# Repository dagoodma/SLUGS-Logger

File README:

SLUGS-Logger

This is the code for a data logger currently being created at the UCSC Autonomous Systems Lab.

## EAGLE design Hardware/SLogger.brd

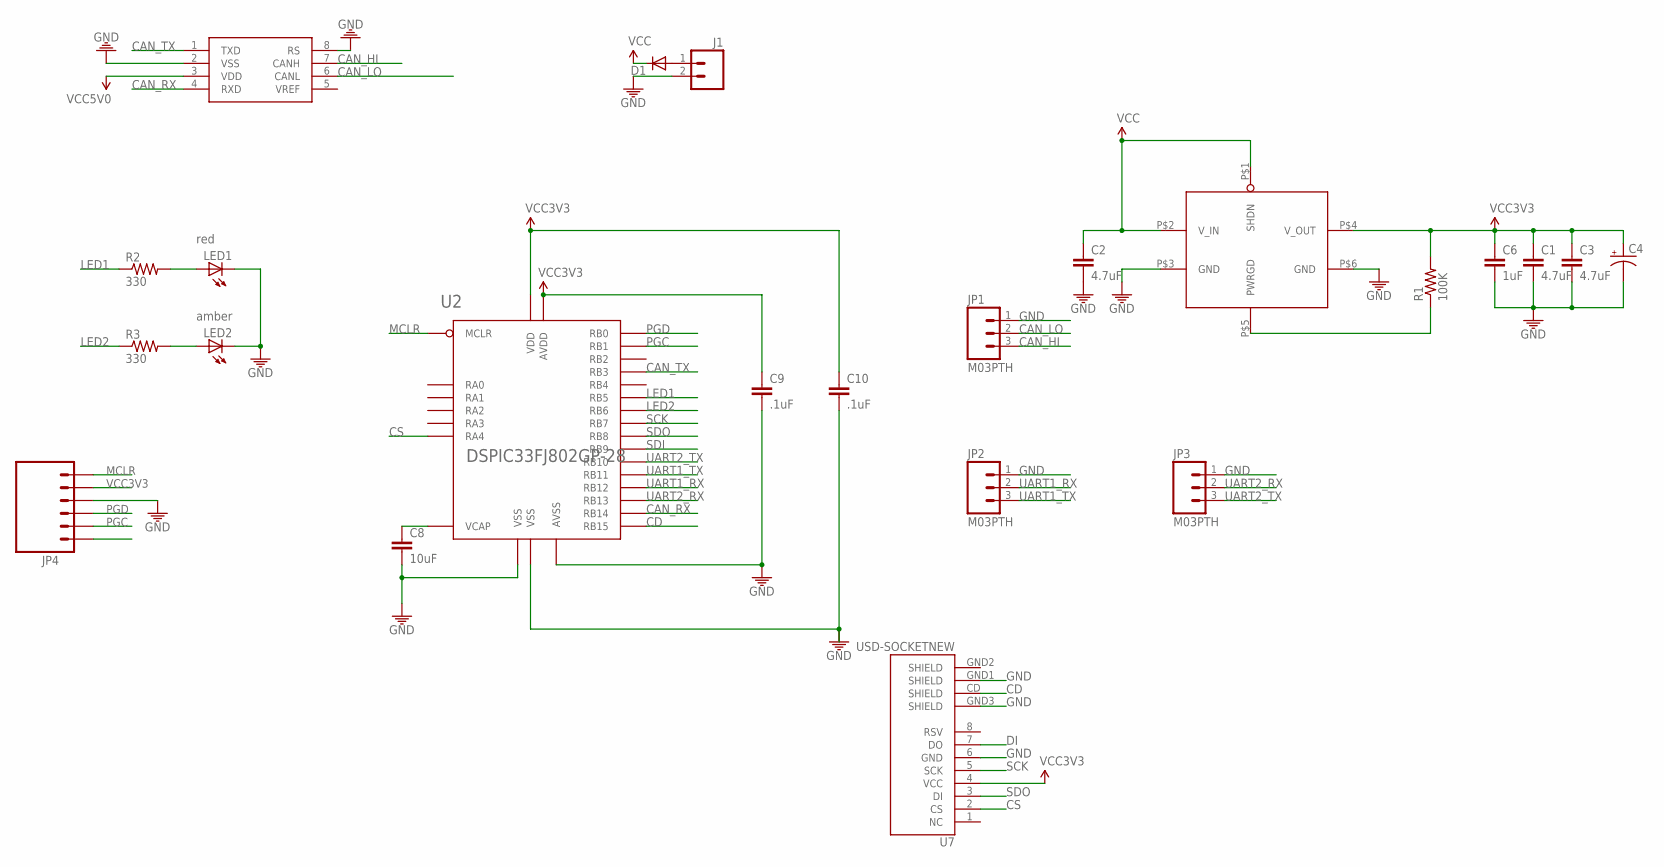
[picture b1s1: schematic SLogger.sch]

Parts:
C1, C2, C3: 4.7uF; 0805
C4: CAP_POLPTH1; CPOL-RADIAL-100UF-25V
C6: 1uF; 0805
C8: 10uF; 0805
C9, C10: .1uF; 0805
D1: DIODESOD; SOD-323F
J1: M02PTH; 1X02
JP1, JP2, JP3: M03PTH; 1X03
JP4: M06LOCK; 1X06_LOCK
LED1, LED2: LED0805; LED-0805
R1: 100K; 0805
R2, R3: 330; 0805
U2: DSPIC33FJ802GP-28; SOIC28-W
U4: MCP2551; SO08
U7: USD-SOCKETNEW; MICRO-SD-SOCKET-PP
U$2: MCP1826; SOT223-5

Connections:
CAN_HI: JP1.3, U4.7 (CANH)
CAN_LO: JP1.2, U4.6 (CANL)
CAN_RX: U2.P$25 (RB14), U4.4 (RXD)
CAN_TX: U2.P$7 (RB3), U4.1 (TXD)
CD: U2.P$26 (RB15), U7.CD (SHIELD)
CS: U2.P$12 (RA4), U7.2 (CS)
DI: U7.7 (DO)
GND: C1.2, C2.2, C3.2, C4.2 (-), C6.2, C8.2, C9.2, C10.2, J1.2 (1), JP1.1, JP2.1, JP3.1, JP4.4, LED1.2 (C), LED2.2 (C), U2.P$8 (VSS), U2.P$19 (VSS), U2.P$27 (AVSS), U4.2 (VSS), U4.8 (RS), U7.6 (GND), U7.GND1 (SHIELD), U7.GND3 (SHIELD)
GND@3: U$2.P$3 (GND)
GND@6: U$2.P$6 (GND)
LED1: R2.1, U2.P$14 (RB5)
LED2: R3.1, U2.P$15 (RB6)
MCLR: JP4.6, U2.P$1 (MCLR)
unnamed: LED1.1 (A), R2.2
unnamed: D1.2 (A), J1.1 (2)
unnamed: LED2.1 (A), R3.2
unnamed: R1.1, U$2.P$5 (PWRGD)
unnamed: C8.1, U2.P$20 (VCAP)
PGC: JP4.2, U2.P$5 (RB1)
PGD: JP4.3, U2.P$4 (RB0)
SCK: U2.P$16 (RB7), U7.5 (SCK)
SDI: U2.P$18 (RB9)
SDO: U2.P$17 (RB8), U7.3 (DI)
UART1_RX: JP2.2, U2.P$23 (RB12)
UART1_TX: JP2.3, U2.P$22 (RB11)
UART2_RX: JP3.2, U2.P$24 (RB13)
UART2_TX: JP3.3, U2.P$21 (RB10)
VCC: C2.1, D1.1 (C), U$2.P$1 (SHDN), U$2.P$2 (V_IN)
VCC3V3: C1.1, C3.1, C4.1 (+), C6.1, C9.1, C10.1, JP4.5, R1.2, U2.P$13 (VDD), U2.P$28 (AVDD), U7.4 (VCC), U$2.P$4 (V_OUT)
VCC5V0: U4.3 (VDD)

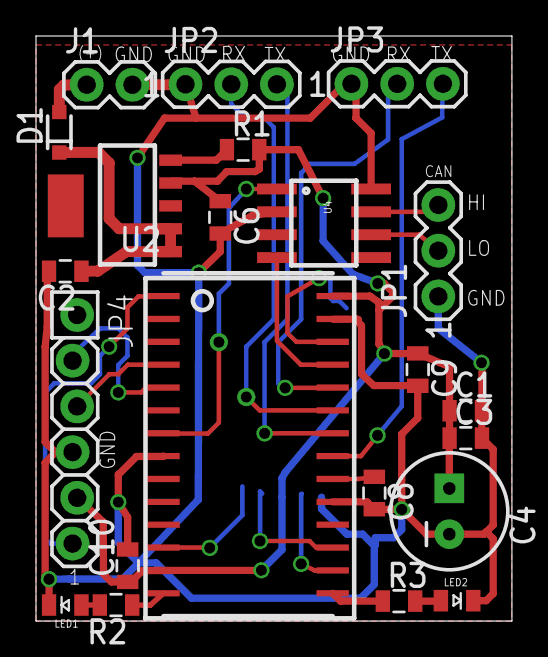
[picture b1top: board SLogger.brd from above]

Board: 2 copper layers, 26.4 x 32.5 mm, 23 parts (1 on the bottom side), 25 nets.

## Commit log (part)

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2013-02-19 Getting used to UART. This does simply receive using DMA.
2013-02-19 Put UART init and interrupt into Uart2.c and Uart2.h
2013-02-19 Put DMA stuff with Uart2 library. DMA is now in ping-pong mode.
2013-02-19 Finished ping-pong buffer with user-defined interrupt func. Uart2Init() now takes a user-defined function pointer which is called when a pin-pong buffer is full. main.c has an example.
2013-02-21 Copied many files from other folders into NewUARTDriver to support Service_SPI.
2013-02-22 Plugged old SPI and Filesystem stuff into new UART using OFBProxy to give Service_SPI() something to use.
2013-02-23 Added NewSDWrite to use unmodified FSIO functions to write to SD.
2013-02-27 Successfully writes multiple sectors into a single cluster. Hacks the FSIO lib.
2013-02-28 Added allocate_multiple_clusters and used it. Doesn't quite work correctly yet with skipping over used clusters.
2013-03-01 Now works with other files in the card and with multiple clusters.
2013-03-02 Added a single-shot sector-write function which does not currently work.
2013-03-05 NewSDWriteSector now works correctly. This easily allows writing a single sectors at a time to a file.
2013-03-05 Added new SDWrite functions to more versatile. They don't currently work. Updated the todo list.
2013-03-05 NewSDWriteSector and NewSDInit now work correctly using the function NewFileUpdate which mimics FSfclose.
2013-03-06 Added TODO.TXT
2013-03-06 More reworking of file system. Redownloaded Microchip lib and removed all old library code.
2013-03-06 Implemented Bryant's circular buffer to work with the UART. It kinda works. Only writes up to 33kb.
2013-03-06 Still getting 33k error, now has debug code. Added debug folder with interesting UART output. Seems there is a problem transitioning between clusters.
2013-03-06 Updated code an debug output, updated debug log to better reflect what is happening.
2013-03-07 33k bug is because of incorrect cluster switching.
2013-03-12 Fixed 33k bug - now correctly switches to a new cluster when needed.
2013-03-12 Data sent while SD is disconnected now is correctly written when the card is reconnected. The fix causes ~30% of sectors to be dropped when writing large files.
2013-03-13 Now only inits the SD card when it is reconnected, not every time we send.
2013-03-14 Added notes file with ideas about states of the card and a thought on allocation efficiency.
2013-03-15 Tested multiple times - each test had indentical errors. Now 38400 baud, removed some debug code.
2013-03-15 Included main.c file for the code used to produce a reliable serial output from a dsPIC33. Added test data and observations.
2013-03-15 Generates own data for putting on the circular buffer. Added more debug notes - a clear pattern was found. Not a problem with serial, DMA, or speed. See third debug note.
2013-03-16 Now the readme isn't totally blank.
2013-03-20 Continued testing to fix circular buffer bug - it is more complicated than expected. Created a python script to confirm a repeating text file.
2013-03-20 Edited readme.
2013-03-20 Changed README file extention to markdown.
2013-04-01 Fixed circular buffer bug, added tests to verify.
2013-04-03 Added more thorough test to CircularBuffer.c and removed a redundant if-else.
2013-04-03 Changed serial sender to send a large amount of text.
2013-04-08 Added checksums on the input and output of the circ buff. There is still a problem with reading from the circ buff.
2013-04-12 Cleaned up CB_Remove() and removed some debug checks.
2013-04-12 More cleanup.
2013-04-12 More cleanup, set things up to do a 3 hour full-speed test.
2013-04-12 Added book.h
2013-04-15 Corrected the circular buffer size for a proper test.
2013-04-17 Set up diagnostic stuff.
2013-04-19 Added projects and such so I can move to another machine.
2013-04-24 Added max buffer output for only the latest clock tick.
2013-04-26 Added more test output and ran some tests. Everything looks fine.
2013-04-26 Started implementing config file. Doesn't work.'
2013-04-30 Correctly reads buad rate from config file.
2013-04-30 Added custom file naming to config.
2013-05-01 Cleaned up a little code. Disconnecting SD sometimes creates a stack or address error.
2013-05-13 Added some tests from earlier.
2013-05-14 Added filename incrementation using the config file. This isn't ideal. Will change it.
2013-05-15 Added some stuff for the new file incrementation. It's not finished and bad.
2013-05-17 Implemented new filename incrementation. Still needs to be thoroughly tested.
2013-05-17 Added an overflow check for the file suffix.
2013-05-17 Did some cleanup, and added a few more checks for various errors, using the FATAl_ERROR() macro. Might add better error handling later.
2013-05-20 Final commit on the Explorer 16. About to convert to CAN Node.
2013-05-20 Haven't gotten it working yet...
2013-06-03 Switched the test sender to a CANode, now everything works fine. Next: UART tests on the CANode.
2013-06-04 There seems to be problems with creating files with the correct names and with the device restarting when the 8GB card is inserted.
2013-06-05 Added a first draft design doc.
2013-07-01 Started making changes for updated requirements. Added header/footer to each sector.
2013-07-01 Opening files is having problems - I implemented basic EEPROM emulation.
2013-07-01 Uses EEPROM to increment file name.
2013-07-02 Implement NewAllocateMultiple into NewSDWriteSector. Need to test.
2013-07-02 Cleaned up some code, moved things around; now NewAllocateMultiple does a NewFileUpdate.
2013-07-02 File writing works with basic tests - file headers and footers are now correct.
2013-07-02 Changed header/footer sizes.
2013-07-03 Started writing a python script to extract data from logs.
2013-07-03 Finished the extractor script.
2013-07-03 Minor change to extractor script.
2013-07-03 Changed helper scripts a little.
2013-07-04 Made a few impovements to the data extraction script.
2013-07-08 Created a new test sender which reads from an SD card for easy diffing, etc. Did some tests, created a large text file which has yet to be sent.
2013-07-11 Began converting to the 33E. Added some tests from before.
2013-07-30 Continued migration
2013-07-30 Still getting it to work.
2013-07-30 UART works now
2013-08-02 Working on fixing the SPI pins.
2013-08-02 SPI seems to work, removed some stuff that didn't need to be tracked.
2013-08-02 Added a doc.
2013-08-02 Changed buffer size.
2013-08-06 Used test project to text SD writing and reading, both work.
2013-08-06 Code is not working or debugging on the main project. Commiting before making drastic changes.
2013-08-07 Still getting this working.
2013-08-08 Made buffer much smaller to hopefully keep the stack out of extended data space. DMA address error soft trap is triggering.
2013-08-13 Added some docs, and put the circular buffer data into EDS.
2013-08-13 Added a doc and tried fixing some of the warnings.
2013-08-14 Added an assembly file to put the stack in regular data space and changed Traps.c
2013-08-14 Changed all the traps from no_auto_psv to auto_psv.
2013-08-14 Increased the buffer and did a short test.
2013-08-14 Added some debug output, and did a long test. Test looks good.
2013-08-15 Isolated a bug with the DEE.
2013-08-15 Added a new flash operations file specifically for the E. This got the DEE lib working. File incrementation works.
2013-08-16 Removed debug stuff from header, edited the extract script accordingly. Removed unused debug variables from main.
2013-08-16 Added debug output over the UART, cleaned up some code, added to the REAME, and did a test.
2013-08-16 Changed the README
2013-08-21 Added more to debug output and changed the README.
2013-09-27 Added to the README, added an image to the docs, and oragnized some files and folders.
2013-09-27 Added more to the README.
2013-09-27 Changed README.
2013-09-27 Changed README more.
2013-09-27 More readme.
2013-09-27 Added a lot of stuff to the README.
2013-09-30 Small readme update
2014-10-07 Rearranged/deleted some files. General cleanup.
2014-10-07 Hardware has inverted card detect signal.
2014-10-07 Removed unnecessary warning.
2014-10-07 Cleaned up the code a bit, nothing major.
2014-10-07 Various improvements and cleanups. Red LED now works. Code is organized a little better. Some dead code removed.
2014-10-07 Deleted a bunch of code/data that shouldn't be there.
2014-10-07 Adding some test files.
2014-10-08 Remove old debugging code. Add LED status blinking.
    Now the amber LED turns off whenever data is received, for a brief point of time. This allows for simple debugging in the field: if the LED isn't blinking, the data isn't being received. And if the S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
2014-10-08 Light the red LED on startup until the card is initialized.
2014-10-08 Renamed data extraction script and refactored it.
    Variable naming is now better.
    More comments.
    Files are properly closed at the end.
    Errors/warnings are more clear.
2014-10-09 Remove unnecessary code.
2014-11-03 Refactor and improve various functionality.
    Implement a more generic and extensible configuration file parser
2014-11-04 Remove BUILTIN_TX as it doesn't make sense.
2014-11-04 Properly parse the last config parameter.
2014-11-04 Only support a single SD-card pin layout.
2014-11-04 Reduce size of temporary character array.
2014-11-04 Fix bug where the next line wasn't properly processed.
2014-11-05 Allow for peripheral pin configuration multiple times.
2014-11-05 Style and code improvements.
2014-11-05 Some more comments and minor code refactoring.
2014-11-05 Refactor a while look to be a more clear and concise if-statement.
2014-11-05 Replace FATAL_ERROR() macro with one that blinks the red LED.
    This makes it more clean when the startup LED is solid at startup and when it
    runs into a fatal error later on during initialization.
2014-11-05 Fix bug with processing the config file.
2014-11-05 Various minor changes to main.c
2014-11-06 Remove use of sprintf() to reduce code space usage and improve performance.
2014-11-06 Added/fixed comments.
2014-11-06 Added a metadata file that stores events that happened during logging.
2014-11-06 Add Uart2Disable() function.
2014-11-06 Disable UART2 when the card is removed.
2014-11-06 Support logging metadata to an additional file.
    Preliminary support added for power-up and config settings.
    Also fix for improper const variable.
2014-11-07 Add a .1s precision timer for logging events.
    And make sure the event trackers are reset everything the card is reinitialized.
2014-11-07 Reorder initialization to prevent bufer overflow.
2014-11-07 Log why a new log file was created.
    Currently tracking if it was a power-on event, card insertion, brown-out, manual reset, or a cat
    ch-all for other unknown events.
2014-11-07 Add a task list.
2014-11-07 Reduce timeout limit in the SPI library.
2014-11-07 Make sure to close any left open metadata/log files before opening new ones.
2014-11-07 Disable the UART when the SD card is removed.
2014-11-07 Change some FATAL_ERRORs into recoverable errors.
    Most errors should be reset once the SDcard is removed and reinserted.
    We just need to make sure that things are reset properly.
2014-11-17 Make extractData.py work on a set of log files.
2014-12-03 Disable SDcard formatting to save 5k of space.
2014-12-03 Move some initialization code until after the file reading.
2014-12-03 Expose Uint16ToHex() and add the inverse HexToUint16().
2014-12-03 Separate the log numbering and log creation code.
2014-12-03 Rely exclusively on pulling the log number from the SD card.
2014-12-03 Remove EEPROM functionality completely.
    Now that card scanning is implemented it's worth using as the only method as it's much
    more robust than the EEPROM stuff is.
2014-12-12 Set the TRIS bits for all used I/O pins.
2014-12-12 Minor readme correction.
2015-01-14 Make extractData.py script Python2.7 compatible.
2015-03-14 Switch status LED to blink @1Hz when normal and 2Hz when receiving data.
2015-03-29 First draft of datalogger hardware board.
2015-03-29 Add notes on testing code.
2015-04-01 Finished 1.0 version of the new SLogger hardware.
